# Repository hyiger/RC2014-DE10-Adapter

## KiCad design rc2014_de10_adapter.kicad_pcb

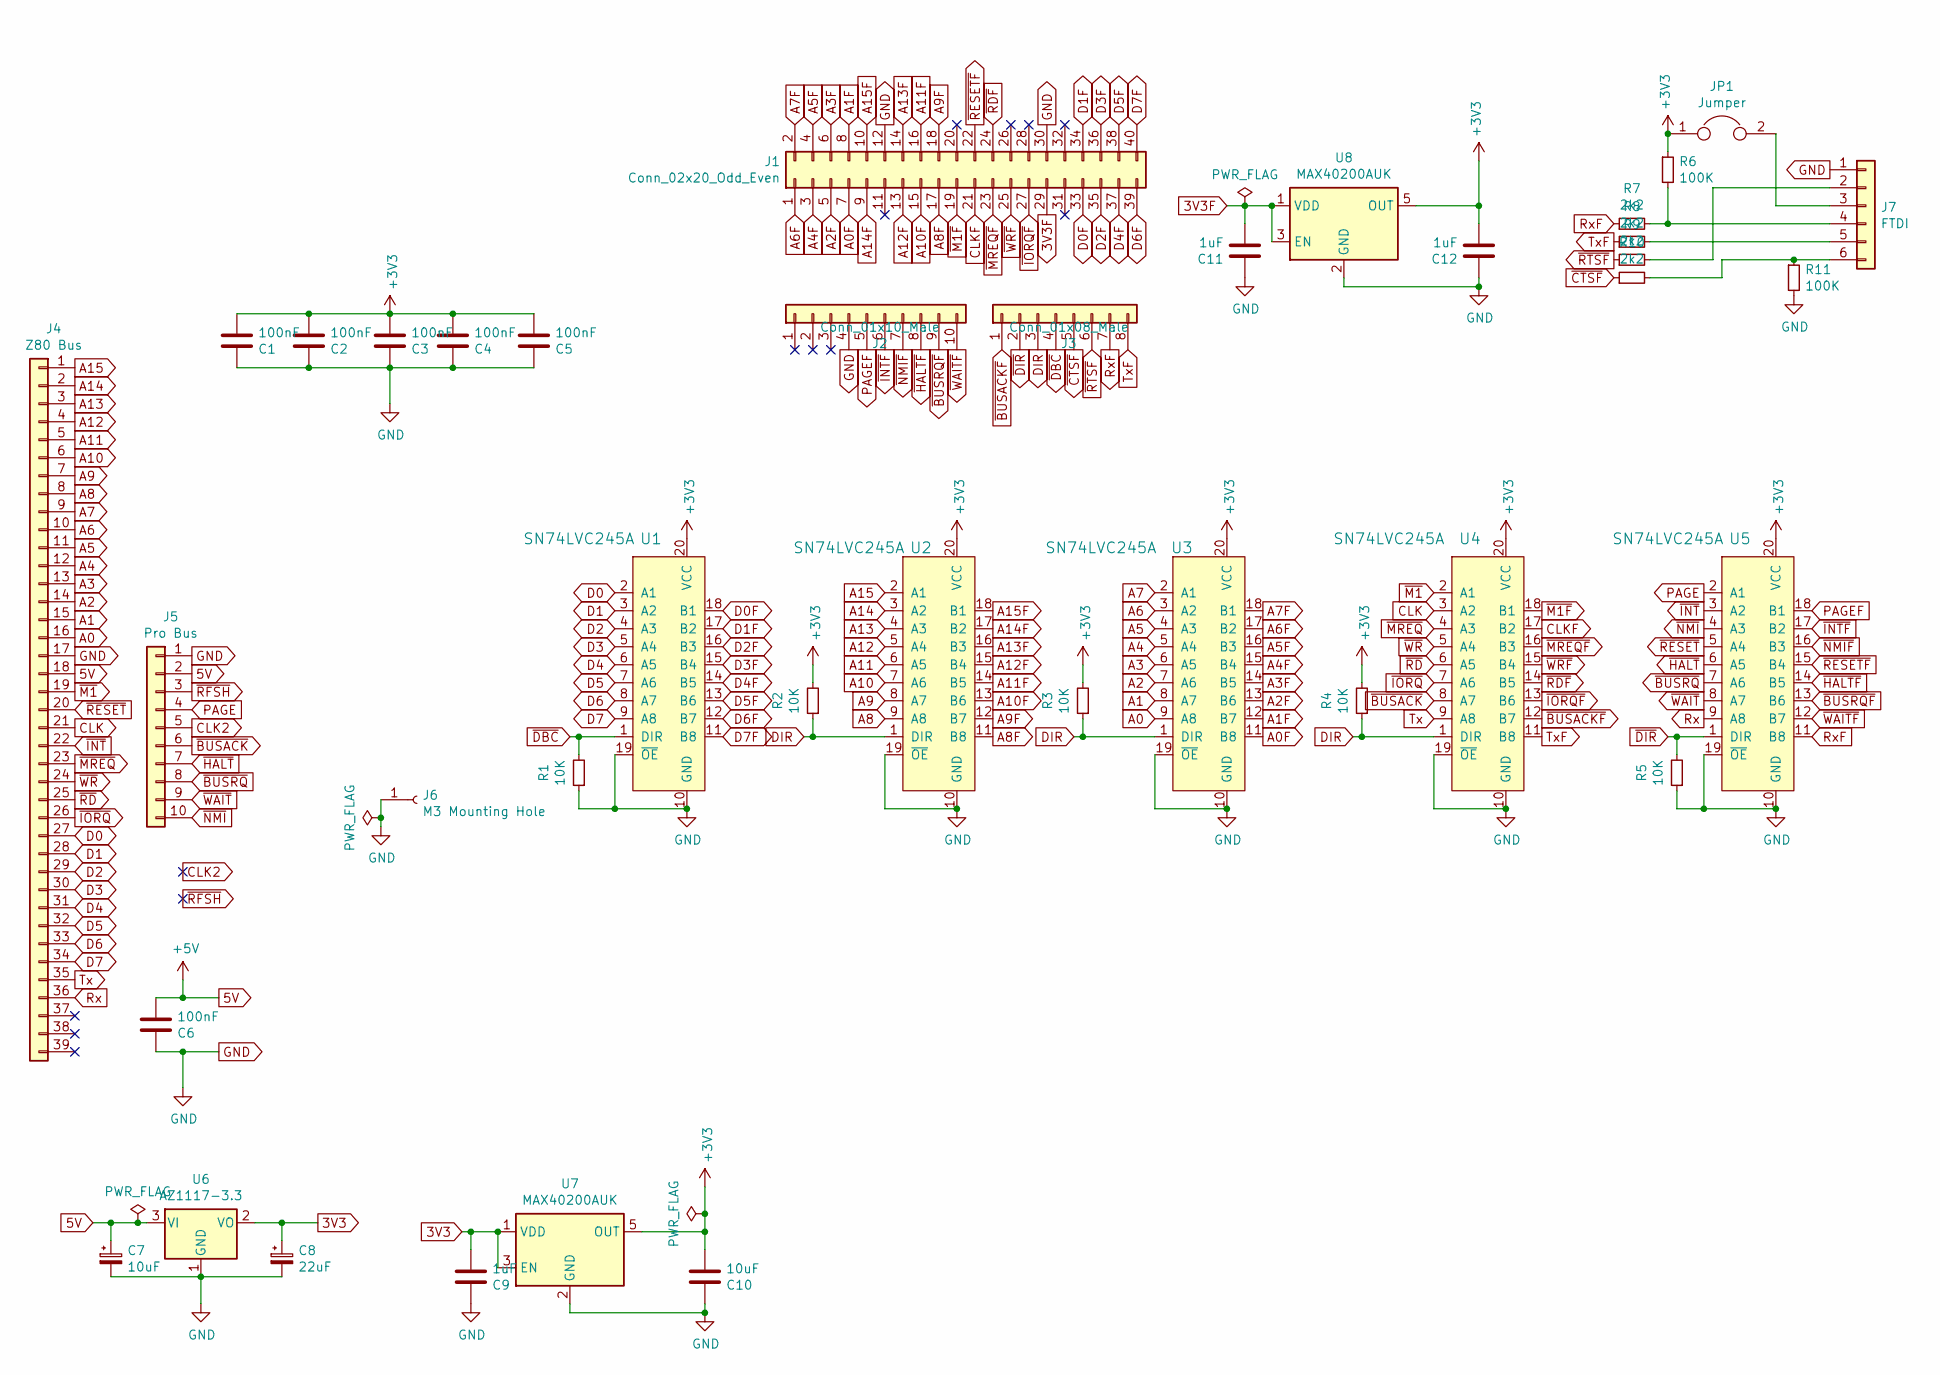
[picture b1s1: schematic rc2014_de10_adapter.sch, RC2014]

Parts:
C1, C2, C3, C4, C5, C6: 100nF; C_0805_2012Metric_Pad1.15x1.40mm_HandSolder; MPN C0805C104K4RACTU
C7: 10uF; C_1206_3216Metric; MPN T520A106M010ATE080
C8: 22uF; C_1206_3216Metric; MPN T520A226M010ATE080
C9, C11, C12: 1uF; C_0805_2012Metric_Pad1.15x1.40mm_HandSolder; MPN C0805C104K4RACTU
C10: 10uF; C_0805_2012Metric_Pad1.15x1.40mm_HandSolder; MPN C0805C104K4RACTU
J1: Conn_02x20_Odd_Even; PinHeader_2x20_P2.54mm_Vertical
J2: Conn_01x10_Male; PinHeader_1x10_P2.54mm_Vertical
J3: Conn_01x08_Male; PinHeader_1x08_P2.54mm_Vertical
J4: Z80 Bus; PinHeader_1x39_P2.54mm_Vertical
J5: Pro Bus; PinHeader_1x10_P2.54mm_Vertical
J6: M3 Mounting Hole; MountingHole_3.2mm_M3_ISO14580_Pad
J7: FTDI; PinHeader_1x06_P2.54mm_Horizontal
JP1: Jumper; PinHeader_1x02_P2.54mm_Vertical
R1, R2, R3, R4, R5: 10K; R_0805_2012Metric_Pad1.15x1.40mm_HandSolder
R6, R11: 100K; R_0805_2012Metric_Pad1.15x1.40mm_HandSolder
R7, R8, R9, R10: 2k2; R_0805_2012Metric_Pad1.15x1.40mm_HandSolder
U1, U2, U3, U4, U5: SN74LVC245A; DIP-20_W7.62mm_Socket; MPN SN74LVC245ADBR; Digi-Key_PN 296-1231-1-ND
U6: AZ1117-3.3; SOT-223-3_TabPin2; MPN AZ1117H-3.3TRE1
U7, U8: MAX40200AUK; SOT-23-5

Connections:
3V3: C8.1, C9.2, U6.2 (VO), U7.1 (VDD), U7.3 (EN)
3V3F: C11.2, J1.29, U8.1 (VDD), U8.3 (EN)
5V: C6.2, C7.1, J4.18, J5.2, U6.3 (VI)
+3V3: C1.2, C2.2, C3.2, C4.2, C5.2, C10.2, C12.2, JP1.1, R2.2, R3.2, R4.2, R6.1, U1.20 (VCC), U2.20 (VCC), U3.20 (VCC), U4.20 (VCC), U5.20 (VCC), U7.5 (OUT), U8.5 (OUT)
A0: J4.16, U3.9 (A8)
A0F: J1.7, U3.11 (B8)
A1: J4.15, U3.8 (A7)
A1F: J1.8, U3.12 (B7)
A2: J4.14, U3.7 (A6)
A2F: J1.5, U3.13 (B6)
A3: J4.13, U3.6 (A5)
A3F: J1.6, U3.14 (B5)
A4: J4.12, U3.5 (A4)
A4F: J1.3, U3.15 (B4)
A5: J4.11, U3.4 (A3)
A5F: J1.4, U3.16 (B3)
A6: J4.10, U3.3 (A2)
A6F: J1.1, U3.17 (B2)
A7: J4.9, U3.2 (A1)
A7F: J1.2, U3.18 (B1)
A8: J4.8, U2.9 (A8)
A8F: J1.17, U2.11 (B8)
A9: J4.7, U2.8 (A7)
A9F: J1.18, U2.12 (B7)
A10: J4.6, U2.7 (A6)
A10F: J1.15, U2.13 (B6)
A11: J4.5, U2.6 (A5)
A11F: J1.16, U2.14 (B5)
A12: J4.4, U2.5 (A4)
A12F: J1.13, U2.15 (B4)
A13: J4.3, U2.4 (A3)
A13F: J1.14, U2.16 (B3)
A14: J4.2, U2.3 (A2)
A14F: J1.9, U2.17 (B2)
A15: J4.1, U2.2 (A1)
A15F: J1.10, U2.18 (B1)
CLK: J4.21, U4.3 (A2)
CLKF: J1.21, U4.17 (B2)
D0: J4.27, U1.2 (A1)
D0F: J1.33, U1.18 (B1)
D1: J4.28, U1.3 (A2)
D1F: J1.34, U1.17 (B2)
D2: J4.29, U1.4 (A3)
D2F: J1.35, U1.16 (B3)
D3: J4.30, U1.5 (A4)
D3F: J1.36, U1.15 (B4)
D4: J4.31, U1.6 (A5)
D4F: J1.37, U1.14 (B5)
D5: J4.32, U1.7 (A6)
D5F: J1.38, U1.13 (B6)
D6: J4.33, U1.8 (A7)
D6F: J1.39, U1.12 (B7)
D7: J4.34, U1.9 (A8)
D7F: J1.40, U1.11 (B8)
DIR: J3.3, R2.1, R3.1, R4.1, U2.1 (DIR), U3.1 (DIR), U4.1 (DIR)
GND: C1.1, C2.1, C3.1, C4.1, C5.1, C6.1, C7.2, C8.2, C9.1, C10.1, C11.1, C12.1, J1.12, J1.30, J2.4, J4.17, J5.1, J6.1, J7.1, R1.1, R5.1, R11.2, U1.10 (GND), U1.19 (~OE), U2.10 (GND), U2.19 (~OE), U3.10 (GND), U3.19 (~OE), U4.10 (GND), U4.19 (~OE), U5.10 (GND), U5.19 (~OE), U6.1 (GND), U7.2 (GND), U8.2 (GND)
unnamed: J7.2, R9.2
unnamed: J7.3, JP1.2
unnamed: J7.4, R6.2, R7.2
unnamed: J7.5, R8.2
unnamed: J7.6, R10.2, R11.1
PAGE: J5.4, U5.2 (A1)
PAGEF: J2.5, U5.18 (B1)
Rx: J4.36, U5.9 (A8)
RxF: J3.7, R7.1, U5.11 (B8)
Tx: J4.35, U4.9 (A8)
TxF: J3.8, R8.1, U4.11 (B8)
~BUSACK: J5.6, U4.8 (A7)
~BUSACKF: J3.1, U4.12 (B7)
~BUSRQ: J5.8, U5.7 (A6)
~BUSRQF: J2.9, U5.13 (B6)
~CTSF: J3.5, R10.1
~DBC: J3.4, R1.2, U1.1 (DIR)
~DIR: J3.2, R5.2, U5.1 (DIR)
~HALT: J5.7, U5.6 (A5)
~HALTF: J2.8, U5.14 (B5)
~INT: J4.22, U5.3 (A2)
~INTF: J2.6, U5.17 (B2)
~IORQ: J4.26, U4.7 (A6)
~IORQF: J1.27, U4.13 (B6)
~M1: J4.19, U4.2 (A1)
~M1F: J1.19, U4.18 (B1)
~MREQ: J4.23, U4.4 (A3)
~MREQF: J1.23, U4.16 (B3)
~NMI: J5.10, U5.4 (A3)
~NMIF: J2.7, U5.16 (B3)
~RD: J4.25, U4.6 (A5)
~RDF: J1.24, U4.14 (B5)
~RESET: J4.20, U5.5 (A4)
~RESETF: J1.22, U5.15 (B4)
~RTSF: J3.6, R9.1
~WAIT: J5.9, U5.8 (A7)
~WAITF: J2.10, U5.12 (B7)
~WR: J4.24, U4.5 (A4)
~WRF: J1.25, U4.15 (B4)

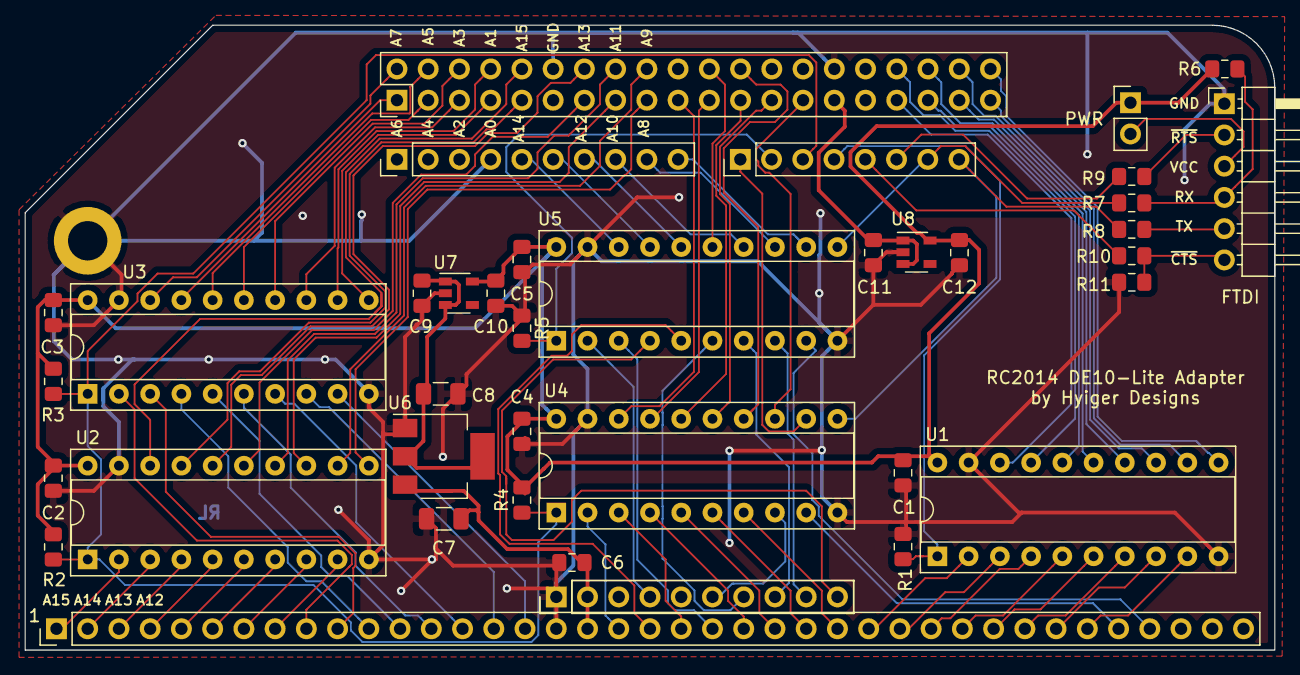
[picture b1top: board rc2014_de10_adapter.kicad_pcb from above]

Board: 2 copper layers, 101.6 x 50.8 mm, 39 parts (0 on the bottom side), 95 nets.

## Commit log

2019-05-07 initial version
2019-05-08 reorganized schematic
2019-05-08 cleanup
2019-05-08 finished routing
2019-05-09 Added FTDI header
2019-05-09 ignore mac specific files
2019-05-09 added direction flags for bus transceivers
2019-05-09 fix caps on ideal diodes
2019-05-11 fixed cap values
